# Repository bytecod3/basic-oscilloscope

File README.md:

# basic-oscilloscope
Basic Digital Storage Oscilloscope

## Introduction
This oscilloscope uses an STM32F103C8T6 blue pill board as the main MPU for processing and display of output

## Specifications
| Spec | Value |
| ----- | -------|
|Analog bandwidth| 0 - 500kHz|
|Number of channels| 2|
|Sample Rate| 2M Samples/s (configurable)|
|RAM| 2GB (External)|
|Processor| STM32F103C8T6|
|CPU-speed| 72MHz|
|Power input| 9V battery of 12V DC jack input|
|Current| 150mA|
|Screen size| 1.8”|
|Maximum input voltage| 50V pk-pk|
|Time base range| 10uS/Div - 500s/Div|
|Storage| USB-2.0 External flash drive|
|Coupling| AC, DC, GND|
|Input impedance| 1MOhm|
|Record length| 1024|

### Top View

### Bottom View

### Left View

### Right View

## Usage
### Powering 
The oscilloscope uses either 12V DC jack adapter or a 9V battery. You can only use one at a time. 
To use the 12V adapter, plug in the jack into the DC Jack located at the top right of the board. To use the 9V battery,
you should have a battery holder with two wires protruding, for +ve and -ve side. Fix these wires on the terminal block located at the top right corner of the board. 
Finally is to toggle the slide-switch located on the right edge of the board.  
On both cases, a green LED should light indicating that the oscilloscope is fully powered. 

To switch off the oscilloscope, toggle the slide-switch agin to the direction labelled OFF on the board silkscreen.

**CAUTION**: Do not use both 12V adapter and 9V at the same time

## Callibration

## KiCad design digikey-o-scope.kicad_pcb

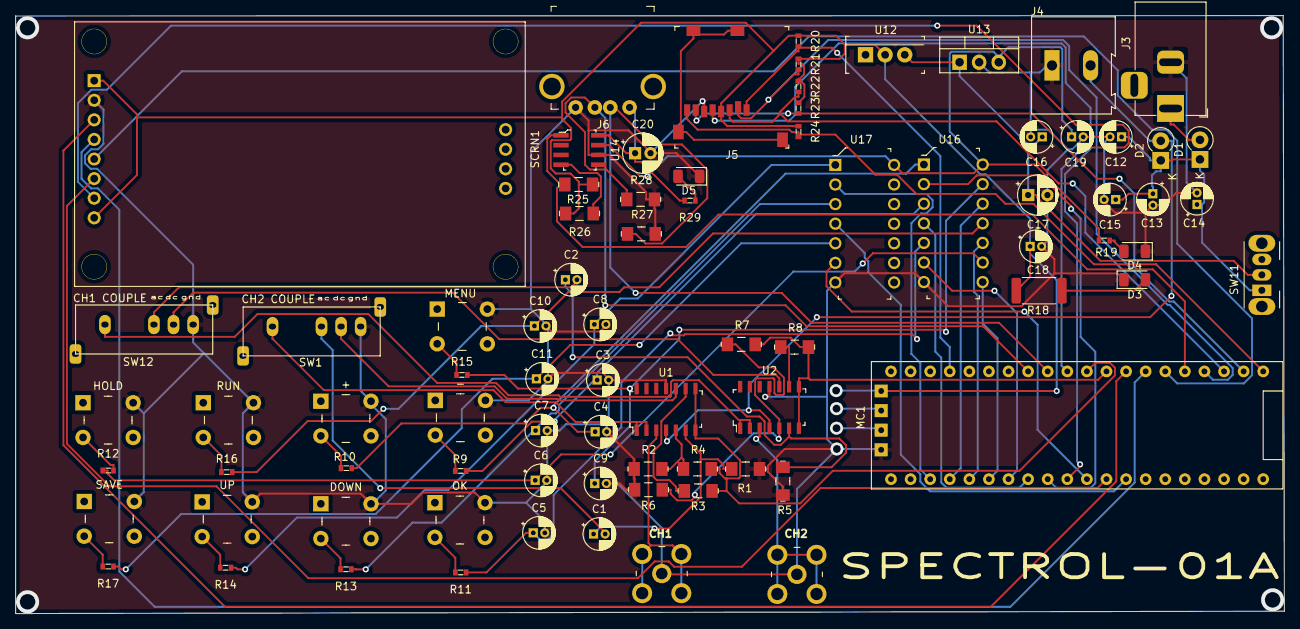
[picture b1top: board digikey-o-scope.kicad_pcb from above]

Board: 2 copper layers, 164.5 x 77.5 mm, 81 parts (0 on the bottom side), 69 nets.

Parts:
+: SW_MEC_5E; Switch_Tactile_THT_6x6mm_MJTP1230
-: SW_MEC_5E; Switch_Tactile_THT_6x6mm_MJTP1230
C1, C2, C3, C4, C5, C6, C7, C8, C9, C10, C11, C19: 0.1u; CP_Radial_D4.0mm_P1.50mm
C12, C13, C14, C15, C16, C18: 100n; CP_Radial_D4.0mm_P1.50mm
C17: 0.22u; CP_Radial_D5.0mm_P2.50mm
C20: 22u; CP_Radial_D5.0mm_P2.00mm
D1, D2: D; D_DO-41_SOD81_P2.54mm_Vertical_KathodeUp
D3, D4, D5: LED; LED_1206_3216Metric
DOWN: SW_MEC_5E; Switch_Tactile_THT_6x6mm_MJTP1230
HOLD: SW_MEC_5E; Switch_Tactile_THT_6x6mm_MJTP1230
J1, J2: 5-1814400-1; RF_SMA_RightAngle_5-1814400-1
J3: 12V IN; BarrelJack_Horizontal
J4: Screw_Terminal_01x02; TerminalBlock_Altech_AK300-2_P5.00mm
J5: Micro_SD_Card; MicroSD_2908-05WB-MG
J6: USB_A; USB_A_Female_UE27AC54100
MC1: BLUE-PILL
MENU: SW_MEC_5E; Switch_Tactile_THT_6x6mm_MJTP1230
OK: SW_MEC_5E; Switch_Tactile_THT_6x6mm_MJTP1230
R1, R2, R3, R4, R5, R6, R7, R8, R25, R26, R27, R28: 10k; 1206
R9, R10, R11, R12, R13, R14, R15, R16, R17, R29: 1k; 0603
R18: 100R; R_2512_6332Metric
R19: 160R; 0603
R20, R21, R22, R23, R24: 22k; 0603
RUN: SW_MEC_5E; Switch_Tactile_THT_6x6mm_MJTP1230
SAVE: SW_MEC_5E; Switch_Tactile_THT_6x6mm_MJTP1230
SCRN1: 1.8"LCD_TFT; 1.8TFT_SCREEN
SW1, SW12: SW_SP3T; SP3T_OS103012MU1QP1_SWITCH
SW11: SPDT; SW_CuK_OS102011MA1QN1_SPDT_Angled
U1, U2: LM324ADR; SOIC-14_W3.9mm
U12: LD1117V33; TO-220-3
U13: LM7805_TO220; TO-220-3_Vertical
U14: LM3526-L; SOIC-8_W3.9mm
U16, U17: SN74HC14N; DIP-14_W3mm
UP: SW_MEC_5E; Switch_Tactile_THT_6x6mm_MJTP1230

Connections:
+: MC1.29, U16.2
+3V3: C18.1, J5.4, MC1.41, R18.1, R20.1, R21.1, R22.1, R23.1, R24.1, R25.1, R26.1, SCRN1.5, SCRN1.12, U12.2
+5V: C19.1, R19.1, U13.3, U14.7, U16.14, U17.14
+9V: D2.2, J4.2, U1.4, U2.4
-: MC1.28, U16.4
CH1_IN: MC1.9, R7.2, R8.2, U2.7, U2.8
CH2_IN: MC1.10, R3.2, R4.2, U1.7, U1.8
DOWN: MC1.33, U17.4
GNDREF: +.2, -.2, C3.2, C4.2, C5.2, C6.2, C7.2, C8.2, C9.2, C10.2, C11.2, C12.2, C13.2, C14.2, C15.2, C16.2, C17.2, C18.2, C19.2, C20.2, D3.1, D4.1, D5.1, DOWN.2, HOLD.2, J1.1, J2.1, J3.2, J4.1, J5.6, J6.4, MC1.44, MENU.2, OK.2, R1.1, R2.1, R5.1, R6.1, R27.2, R28.2, RUN.2, SAVE.2, SCRN1.6, SW1.4, SW12.4, U1.11, U2.11, U13.2, U14.6, U16.7, U17.7, UP.2
HOLD: MC1.26, U16.8
MENU: MC1.24, U16.12
unnamed: C1.1, R1.2, U1.6
unnamed: C2.1, R5.2, U2.6
unnamed: C3.1, R9.1, U16.3
unnamed: C4.1, R10.1, U16.1
unnamed: C5.1, R11.1, U16.5
unnamed: C6.1, R12.1, U16.9
unnamed: C7.1, R13.1, U17.3
unnamed: C8.1, R14.1, U17.1
unnamed: C9.1, R15.1, U16.13
unnamed: C10.1, R16.1, U16.11
unnamed: C11.1, R17.1, U17.5
unnamed: C12.1, C13.1, C14.1, C15.1, D1.1, D2.1, SW11.1
unnamed: C16.1, C17.1, SW11.2, U12.3, U13.1
unnamed: C20.1, J6.1, R29.2, U14.8
unnamed: D1.2, J3.1
unnamed: D3.2, R18.2
unnamed: D4.2, R19.2
unnamed: D5.2, R29.1
unnamed: J1.2, U1.3
unnamed: J2.2, U2.3
unnamed: R2.2, R4.1, U1.5
unnamed: R3.1, U1.9
unnamed: R6.2, R7.1, U2.5
unnamed: R8.1, U2.9
unnamed: -.3, R9.2
unnamed: +.3, R10.2
unnamed: OK.3, R11.2
unnamed: HOLD.3, R12.2
unnamed: DOWN.3, R13.2
unnamed: R14.2, UP.3
unnamed: MENU.3, R15.2
unnamed: R16.2, RUN.3
unnamed: R17.2, SAVE.3
unnamed: R26.2, U14.4
OK: MC1.27, U16.6
PA5: J5.5, MC1.30
PA7: MC1.32, SCRN1.10
PA8: MC1.5, R25.2, U14.1
PA9: MC1.6, SCRN1.9
PA10: MC1.7, SCRN1.8
PA11: MC1.8, SCRN1.7
PB3: MC1.11, SCRN1.11
PB4: J6.2, MC1.12, R27.1
PB5: J6.3, MC1.13, R28.1
PB9: J5.1, MC1.17, R20.2
PB12: J5.8, MC1.1, R24.2
PB13: J5.7, MC1.2, R23.2
PB14: J5.3, MC1.3, R22.2
PB15: J5.2, MC1.4, R21.2
RUN: MC1.25, U16.10
SAVE: MC1.31, U17.6
UP: MC1.23, U17.2
ac1: C2.2, SW12.1
ac2: C1.2, SW1.1
couple1: SW12.3, U2.1, U2.2
couple2: SW1.3, U1.1, U1.2
dc1: SW12.2, U2.10
dc2: SW1.2, U1.10

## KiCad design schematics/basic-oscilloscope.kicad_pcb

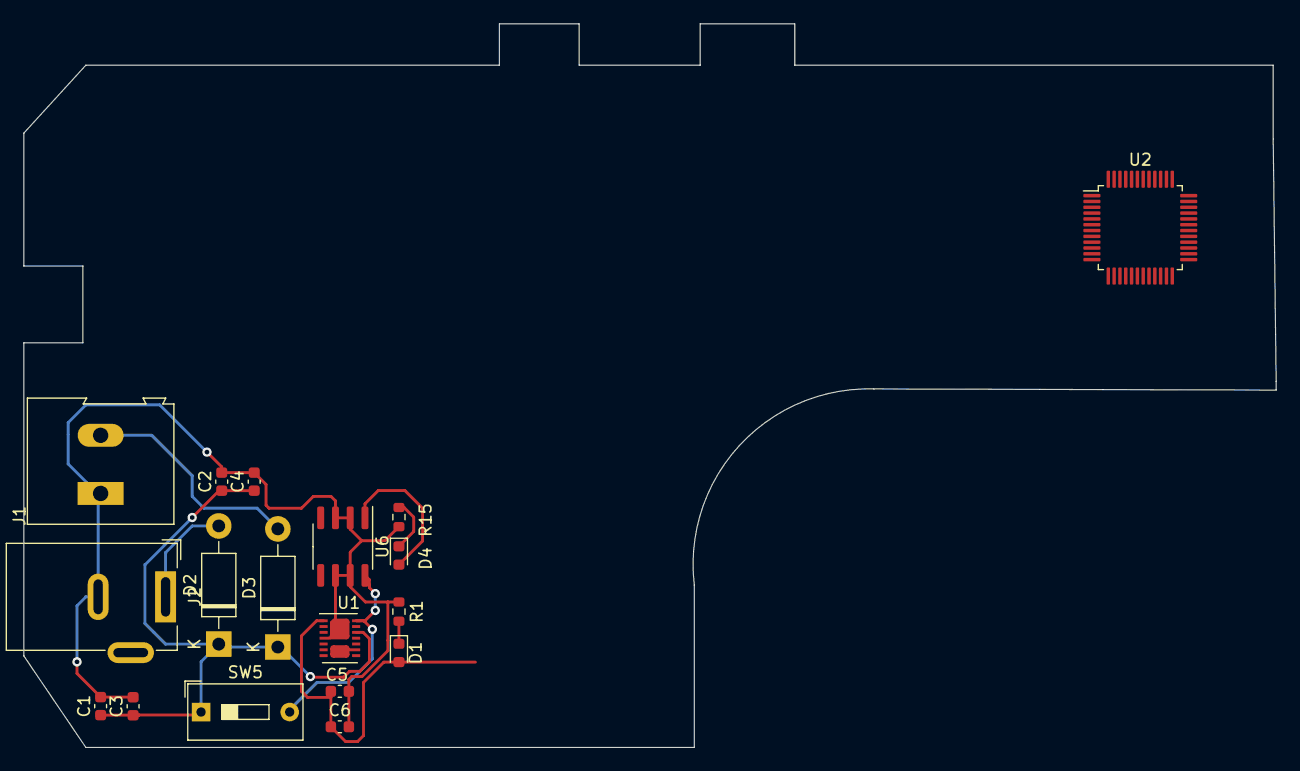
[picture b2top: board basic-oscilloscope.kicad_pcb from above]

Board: 2 copper layers, 107.7 x 62.2 mm, 18 parts (0 on the bottom side), 9 nets.

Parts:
C1, C6: 100n; C_0603_1608Metric
C2, C4: CP; C_0603_1608Metric
C3, C5: 10u; C_0603_1608Metric
D1, D4: LED; D_0603_1608Metric
D2, D3: 1N4001; D_DO-41_SOD81_P10.16mm_Horizontal
J1: 9V_BATTERY; TerminalBlock_Altech_AK300-2_P5.00mm
J2: 12V_DC_JACK; BarrelJack_Wuerth_6941xx301002
R1, R15: 200; R_0603_1608Metric
SW5: SW_SPST; SW_DIP_SPSTx01_Slide_9.78x4.72mm_W7.62mm_P2.54mm
U1: LT3032-3.3; Linear_DE14MA
U2: STM32F103C8Tx; LQFP-48_7x7mm_P0.5mm
U6: LM78L05_SO8; SOIC-8_3.9x4.9mm_P1.27mm

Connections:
0: C1.2, C2.2, C3.2, C4.2, C5.2, C6.2, J1.1, J2.2, R1.2, R15.2, U1.4, U2.8, U2.23, U2.35, U2.47, U6.2, U6.3, U6.6, U6.7
3.3V: C5.1, C6.1, D1.2, U1.1, U2.9, U2.24, U2.36, U2.48
5V: D4.2, U6.1
unnamed: C1.1, C2.1, C3.1, C4.1, D2.1, D3.1, SW5.1, U1.12
unnamed: SW5.2, U1.14, U6.8
unnamed: D1.1, R1.1
unnamed: D2.2, J2.1
unnamed: D3.2, J1.2
unnamed: D4.1, R15.1

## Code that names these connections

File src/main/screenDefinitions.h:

/* Definitions for screen pins going into the STM32 Board */

#define SCK 	PB3
#define SDA 	PA7
#define DC		PA9 // A0
#define RESET 	PA10
#define CS		PA11

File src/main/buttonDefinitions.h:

#ifndef BUTTONDEFINITIONS _H
#define BUTTONDEFINITIONS _H

/* button pin definitions */
#define MENU  PC13
#define OK    PA2
#define PLUS  PA4
#define MINUS PA3
#define UP    PC14 
#define DOWN  PB0
#define SAVE  PA6
#define HOLD  PA1
#define RUN   PA0

/* Initial status settings */
unsigned int initial_button_status = 0x0;

/* debounce handling */
long TIME = 0;
long DEBOUNCE_DELAY = 200; // to check this callbration

#endif

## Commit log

2021-07-16 power supply branching
2021-07-17 implement reset and debounce
2021-07-18 add hardware debounce
2021-07-22 add voltage buffer for BNC channels
2021-07-22 add 5V label for buffer
2021-08-12 create pcb layout
2021-09-02 update component footprints
2021-10-12 add hierachical schematics
2021-10-12 update readmee
2021-10-13 add control button test
2021-10-23 add button control library for screen control
2021-10-23 create TFT screen definition and instance
2021-10-25 add button definitions
2021-10-25 add working code for buttons
2021-11-03 create tft-simulation GUI
2021-11-04 add screen simulator
2022-05-14 added power supply simulations
